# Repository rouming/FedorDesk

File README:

NAME
    FedorDesk -- firmware for toy with 3 buttons, 12 leds and 1 mario-theme
    sound.

AUTHOR
    Roman Pen

USERS
    son Fedor

ACKNOWLEDGEMENTS
COPYRIGHT & LICENSE
    Copyright 2012 Roman Pen

    This program is free software; you can redistribute it and/or modify it
    under the terms of either: the GNU General Public License as published
    by the Free Software Foundation

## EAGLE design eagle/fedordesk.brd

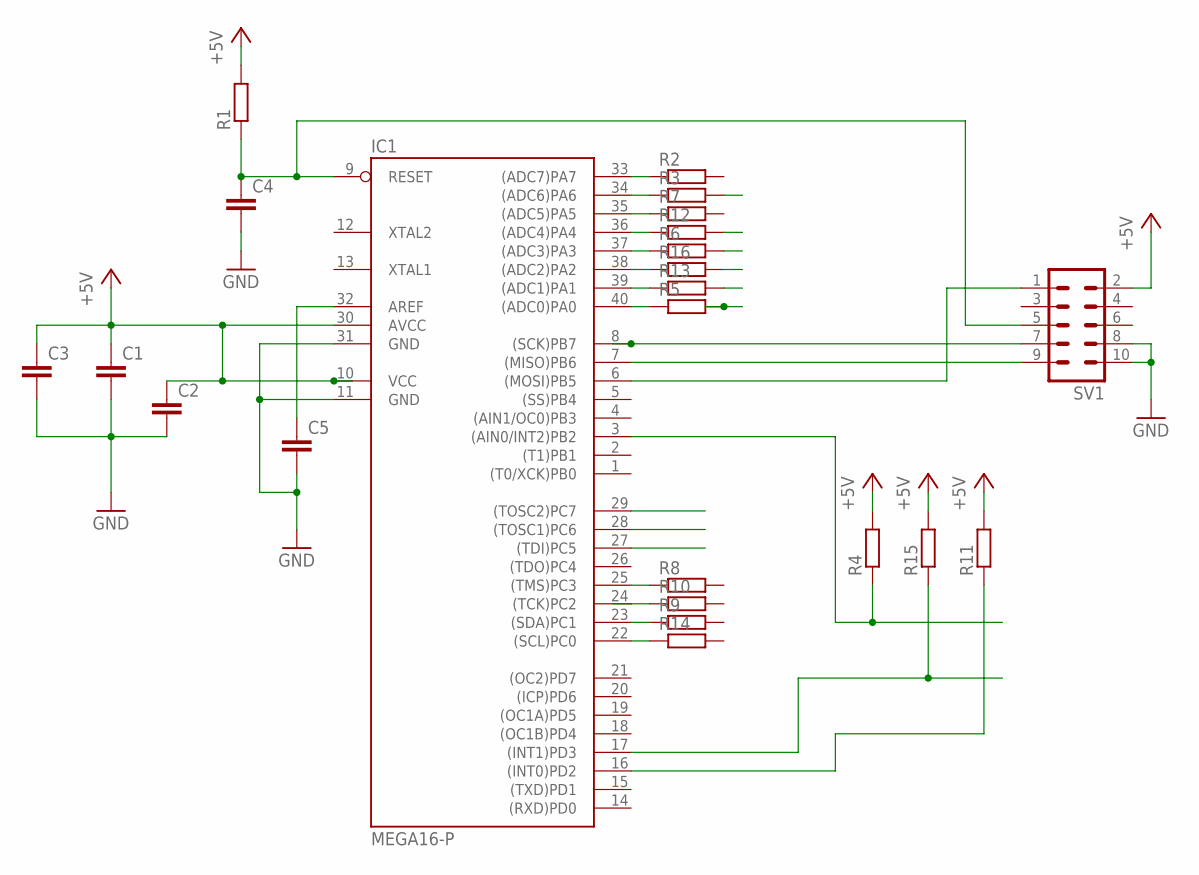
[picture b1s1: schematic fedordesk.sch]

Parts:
C1, C2, C3, C4, C5: C-EU050-024X044; C050-024X044
IC1: MEGA16-P; DIL40
R1, R2, R3, R4, R5, R6, R7, R8, R9, R10, R11, R12, R13, R14, R15, R16: R-EU_0207/10; 0207/10
SV1: ML10L

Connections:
+5V: C1.1, C2.1, C3.1, IC1.10 (VCC), IC1.30 (AVCC), R1.2, R4.2, R11.2, R15.2, SV1.2
GND: C1.2, C2.2, C3.2, C4.2, C5.2, IC1.11 (GND), IC1.31 (GND), SV1.8, SV1.10
unnamed: IC1.3 ((AIN0/INT2)PB2), R4.1
unnamed: C5.1, IC1.32 (AREF)
unnamed: IC1.17 ((INT1)PD3), R15.1
unnamed: IC1.16 ((INT0)PD2), R11.1
unnamed: IC1.6 ((MOSI)PB5), SV1.1
unnamed: C4.1, IC1.9 (RESET), R1.1, SV1.5
unnamed: IC1.8 ((SCK)PB7), SV1.7
unnamed: IC1.7 ((MISO)PB6), SV1.9
unnamed: IC1.33 ((ADC7)PA7), R2.1
unnamed: IC1.34 ((ADC6)PA6), R3.1
unnamed: IC1.35 ((ADC5)PA5), R7.1
unnamed: IC1.36 ((ADC4)PA4), R12.1
unnamed: IC1.37 ((ADC3)PA3), R6.1
unnamed: IC1.38 ((ADC2)PA2), R16.1
unnamed: IC1.39 ((ADC1)PA1), R13.1
unnamed: IC1.40 ((ADC0)PA0), R5.1
unnamed: IC1.25 ((TMS)PC3), R8.1
unnamed: IC1.23 ((SDA)PC1), R9.1
unnamed: IC1.22 ((SCL)PC0), R14.1
unnamed: IC1.24 ((TCK)PC2), R10.1

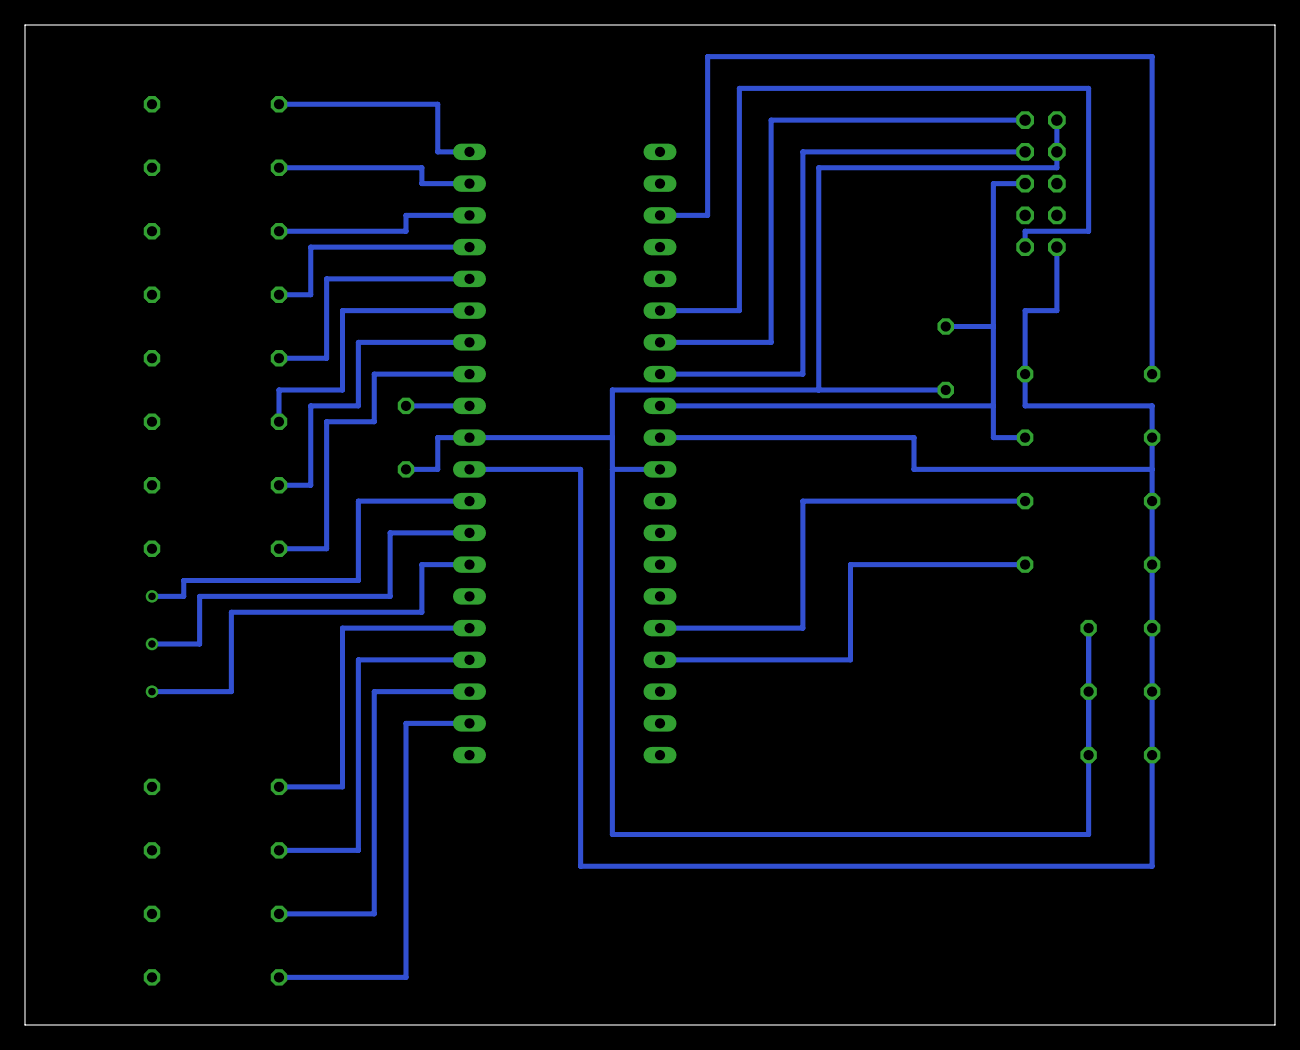
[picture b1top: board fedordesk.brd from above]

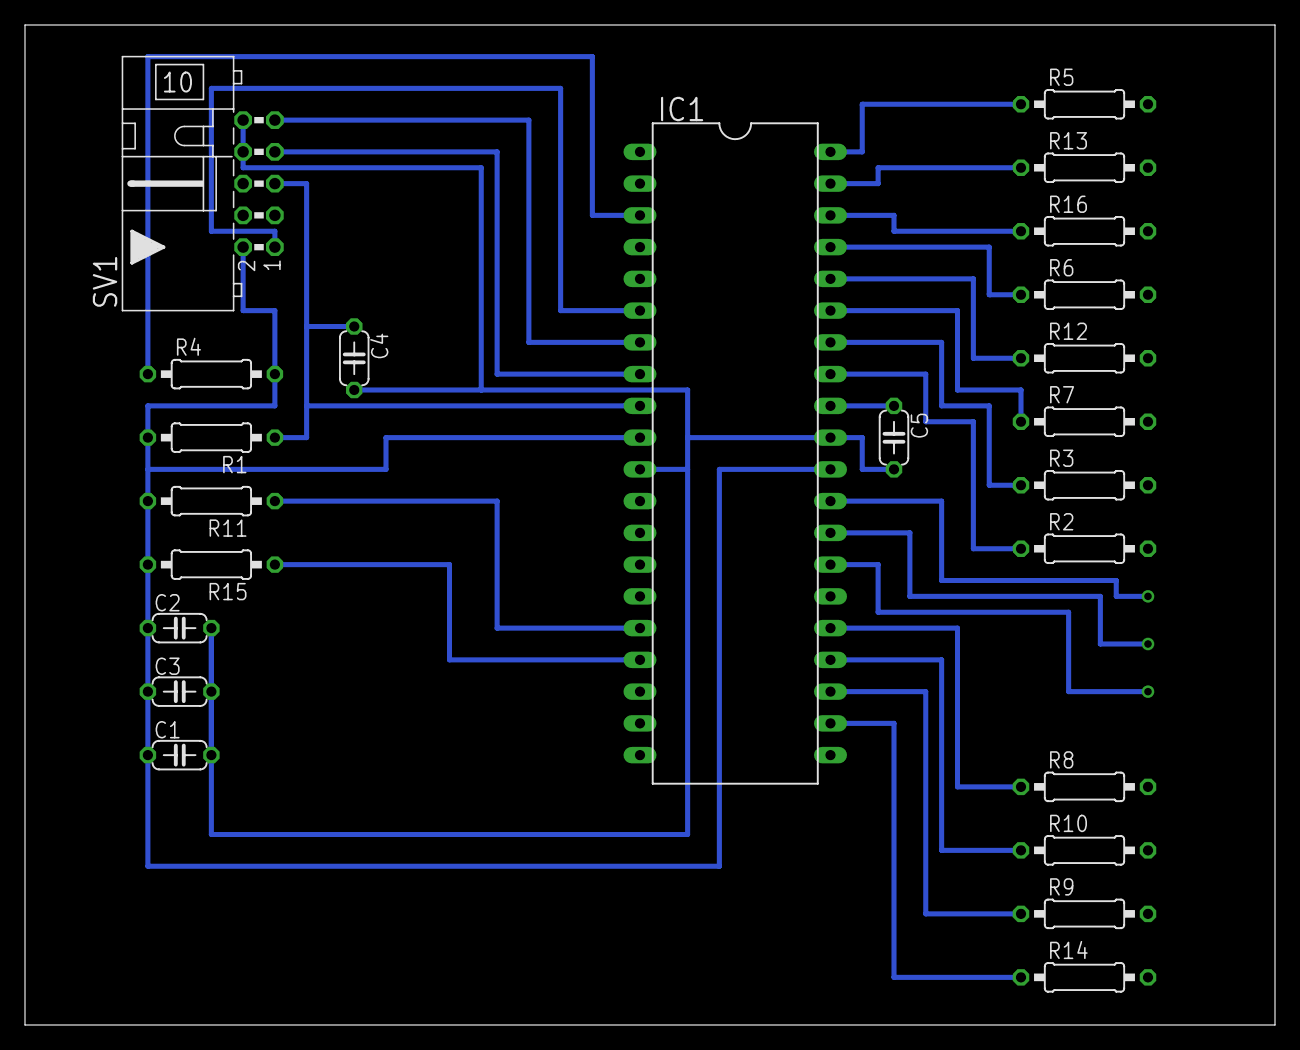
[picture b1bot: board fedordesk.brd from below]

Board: 2 copper layers, 100.0 x 80.0 mm, 23 parts (23 on the bottom side), 22 nets.

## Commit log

2012-04-01 add skeleton of fedor desk
2012-04-03 explicitly set standard c99 to makefile
2012-04-03 finish with leds
2012-04-03 fix lost bit for last led
2012-04-03 fix mode change
2012-04-03 simplify bits check
2012-04-03 add some useful links
2012-04-05 fix building for atmega16
2012-04-05 fix timer#0 enabling, fix prescaler according to 1MHz
2012-04-05 drop ground at any call hw_fire_leds
2012-04-05 increase counter from 8-bit to 16
2012-04-05 fire leds fixes
2012-04-16 save power with persistence of vision
    i.e. never fire on all leds, but try to do frequent flickering.
    every time we have only one led on (current ~20mA)
2012-04-16 fix timer interrupts when prescaler is off
2012-04-22 update proteus scheme and sources, change ground wires
2012-05-04 Add hex extracting dependence and avrdude burning cmd
2012-05-04 Avoid sudo when using avrdude, just create udev rule
2012-05-04 Makefile comments tweaks
2012-05-04 Makefile udev comments tweaks
2012-05-05 Add F_CPU define
2012-05-10 Now ground is turned by H not by L
2012-05-10 increase max turned on pins to 6
2012-05-11 count 100ms in timer more accurate
2012-05-16 wrong param, should be void
2012-05-16 increase default leds speed
2012-05-18 Generating hex just on flash rule, also read fuses cmd
2012-05-19 remove big delay of while in timer interrupt
2012-05-19 makefile tweaks
2012-05-19 timer0 in CTC mode, i.e. it fires not by 8-bit overflow (256) but when TCNT0 == OCR0
2012-05-20 audio playing implementation on PWM using timer2
2012-05-21 update isis scheme
2012-05-21 for firing leds and sound sampling use 16-bit timer1 instead of 8-bit timer0
2012-05-21 minor sample rate correction (forgotten -1)
2012-05-21 fix prescaler for timer1
2012-05-21 update sounddata. now it says 'it's working' by woman
2012-05-21 change cpu frequency from 1Mhz to 8Mhz
2012-05-21 super mario as sound data
2012-05-22 minor code tweaks
2012-05-22 implement deinition procedure for PWM timer2
2012-05-22 some fuses tweaks in makefile and in sources
2012-05-30 add README file for github
2012-06-17 toggle start/stop playback on button press
2012-06-17 add eagle scheme and board projects
2012-06-18 rename fedor_desk.DSN -> proteus/fedordesk.dsn
